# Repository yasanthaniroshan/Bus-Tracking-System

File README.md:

# Bus Tracking System

This is a project with location tracker attached to bus and Django based website for handling the whole Tracking System

## Run Locally

Clone the project

```bash
  git clone https://github.com/yasanthaniroshan/Bus-Tracking-System.git
```

Install dependencies

```bash
  pip install -r requirements.txt
```

Start the server

```bash
  python manage.py runserver
```

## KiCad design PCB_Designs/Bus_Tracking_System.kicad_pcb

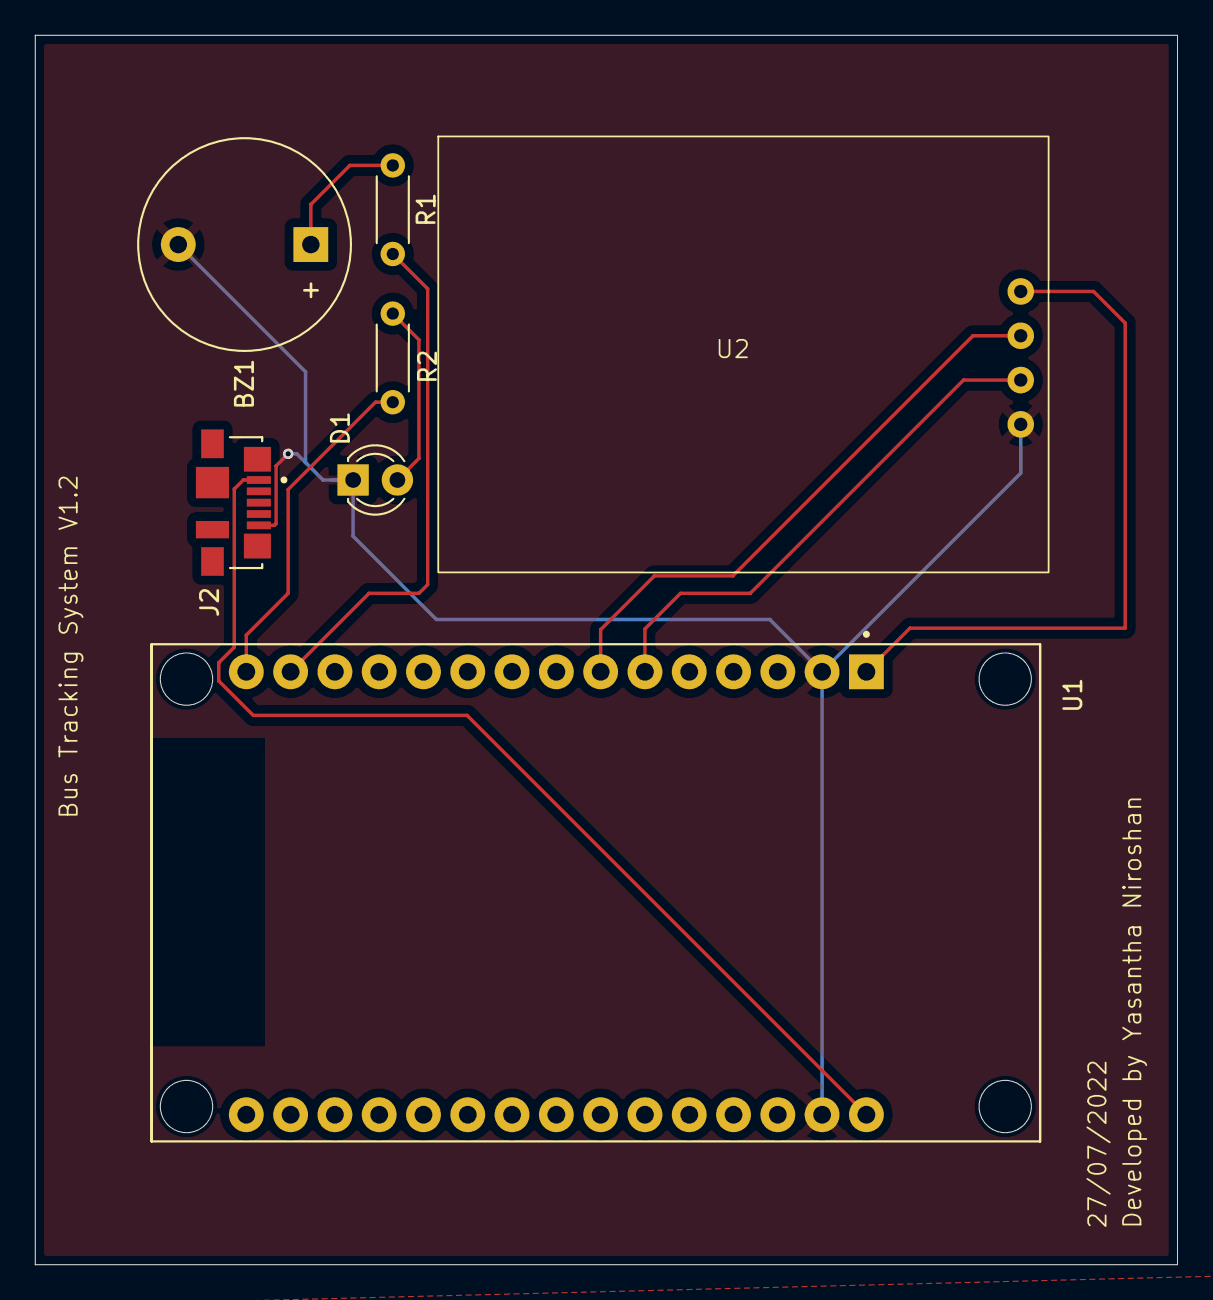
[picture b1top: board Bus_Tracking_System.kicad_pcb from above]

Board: 2 copper layers, 65.5 x 70.5 mm, 7 parts (0 on the bottom side), 9 nets.

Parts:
BZ1: Buzzer; Buzzer_12x9.5RM7.6
D1: LED; LED_D3.0mm_Clear
J2: 47346-0001; MOLEX_47346-0001
R1, R2: 1k; R_Axial_DIN0204_L3.6mm_D1.6mm_P5.08mm_Horizontal
U1: ESP32-DEVKIT-V1; MODULE_ESP32_DEVKIT_V1
U2: NEO_6M_THT

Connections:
+3.3V: U1.1 (3V3), U2.1 (Vcc)
+5V: J2.1 (VBUS), U1.30 (VIN)
/Buzz: R1.2, U1.14 (D22)
/LED_Sig: R2.1, U1.15 (D23)
/Rx: U1.6 (RX2), U2.3 (Tx)
/Tx: U1.7 (TX2), U2.2 (Rx)
GND: BZ1.2 (-), D1.1 (K), J2.5 (GND), U1.2 (GND), U1.29 (GND), U2.4 (GND)
unnamed: BZ1.1 (+), R1.1
unnamed: D1.2 (A), R2.2

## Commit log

2022-06-27 ready to publish
2022-06-27 copy and moved
2022-06-27 deleted runtime
2022-06-27 removing line in requirement.txt
2022-06-27 edited requirement .txt
2022-06-27 changine basedr
2022-06-27 base dir
2022-06-27 removing line
2022-06-27 debug = false and procfile port
2022-06-27 removing unnessary files
2022-06-27 removing un nessary files 2
2022-06-27 changing port to ${PORT}
2022-06-27 adding a host
2022-06-27 static files error
2022-06-27 collect static files
2022-06-27 stylesheet correcting
2022-06-27 whitenoise for static files
2022-06-27 added trusted origin
2022-06-27 changing files to log into admin
2022-06-27 adding django setting
2022-06-27 changing https to NOne
2022-06-27 adding https
2022-06-28 removing django-heroku
2022-06-28 Debug = True
2022-06-28 adding migrate command
2022-06-28 adding database config
2022-06-28 changing database congfigs
2022-06-28 removing databse configs
2022-06-28 changing line
2022-06-28 i can't understand whats wrong with it
2022-06-28 removed line
2022-06-28 changing database auth
2022-06-28 fixed index of list
2022-07-01 after much changes
2022-07-01 in dashborad removed unv=wanted line
2022-07-01 change to pagekite.me
2022-07-01 added "Content-Type": "application/json"
2022-07-01 with cors
2022-07-01 added no-cors
2022-07-02 added new line
    'Access-Control-Allow-Methods', 'GET, POST, PUT, DELETE, OPTIONS'
2022-07-02 added ,
2022-07-02 changed "" to ''
2022-07-02 changed origin to heroku
2022-07-02 removed content typr parameter in header
2022-07-02 removed contet type in views.py
2022-07-02 swaped latitude ,longitude in js
2022-07-02 console print addded
2022-07-02 swaped again current_altitude, current_altitude
2022-07-02 added console.log line
2022-07-02 i want some rest :(
2022-07-02 removed map.setCenter(location_of_bus); line
2022-07-02 chaning frontpage to mobile responsive
2022-07-02 started
2022-07-02 chnaged > to <
2022-07-02 remove line after tat
2022-07-02 print line added
2022-07-02 added = for ==
2022-07-02 added python code to free time
2022-07-02 addded get element by id
2022-07-02 updated requirements.txt
2022-07-02 updated js file
2022-07-02 change to cosole for print
2022-07-02 added id to html
2022-07-02 changed initial value
2022-07-02 updated minutes and hours
2022-07-02 changed frontend css for mobile responsiveness
2022-07-02 remove un wanted lines in html
2022-07-02 sub route number corrected
2022-07-02 make mobile responsive in location.html
2022-07-02 renamed styleforlocation.css
2022-07-02 renamed here in static file
2022-07-02 renamed static file intemplate
2022-07-02 Rename stylesforlocation.css to styleseditedforlocation.css
2022-07-02 added media file
2022-07-02 reanmed
2022-07-02 corrected here also
2022-07-03 image added for serverfor servey
2022-07-03 added image after renaming
2022-07-03 added survey template and view
2022-07-18 Changed database credentials
    Changed database credentials
2022-08-12 before final
2022-08-12 adding tour details -1
2022-08-12 changing location.css for mobile
2023-10-05 updated documentation
2024-05-24 Added Modifications - Changed the file structure
2024-05-24 Modified Documentation - Added Cover - Modified Readme
2024-05-24 Modifications to Docs - Added New Images - Added Reviews
2024-07-10 Added PCB Designs - All the PCB Designs using KiCad
2024-07-10 Added 3D view of PCB Design
